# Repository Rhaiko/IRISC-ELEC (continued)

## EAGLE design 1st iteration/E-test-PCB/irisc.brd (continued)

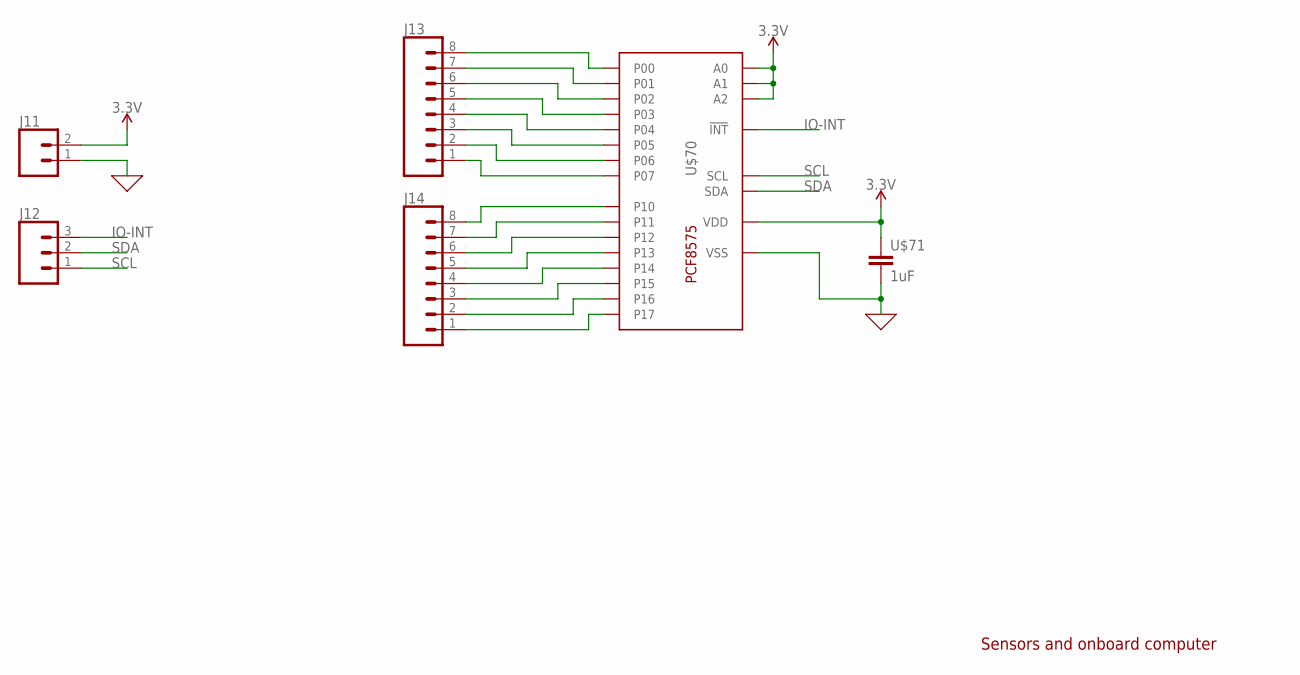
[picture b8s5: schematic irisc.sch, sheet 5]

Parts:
J11: CONN_02; 1X02
J12: CONN_03; 1X03
J13, J14: CONN_08"; 1X08
U$70: PCF8575CSSOP24N; SOP65P810X120-24
U$71: 1uF; RESC0603_N

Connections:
0: J11.1, U$70.12 (VSS), U$71.2; also elsewhere on the board
3.3V: J11.2, U$70.2 (A1), U$70.3 (A2), U$70.21 (A0), U$70.24 (VDD), U$71.1; also elsewhere on the board
IO-INT: J12.3, U$70.1 (!INT)
unnamed: J13.8, U$70.4 (P00)
unnamed: J13.7, U$70.5 (P01)
unnamed: J13.6, U$70.6 (P02)
unnamed: J13.5, U$70.7 (P03)
unnamed: J13.4, U$70.8 (P04)
unnamed: J13.3, U$70.9 (P05)
unnamed: J13.2, U$70.10 (P06)
unnamed: J13.1, U$70.11 (P07)
unnamed: J14.8, U$70.13 (P10)
unnamed: J14.7, U$70.14 (P11)
unnamed: J14.6, U$70.15 (P12)
unnamed: J14.5, U$70.16 (P13)
unnamed: J14.4, U$70.17 (P14)
unnamed: J14.3, U$70.18 (P15)
unnamed: J14.2, U$70.19 (P16)
unnamed: J14.1, U$70.20 (P17)
SCL: J12.1, U$70.22 (SCL); also elsewhere on the board
SDA: J12.2, U$70.23 (SDA); also elsewhere on the board

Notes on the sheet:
Sensors and onboard computer

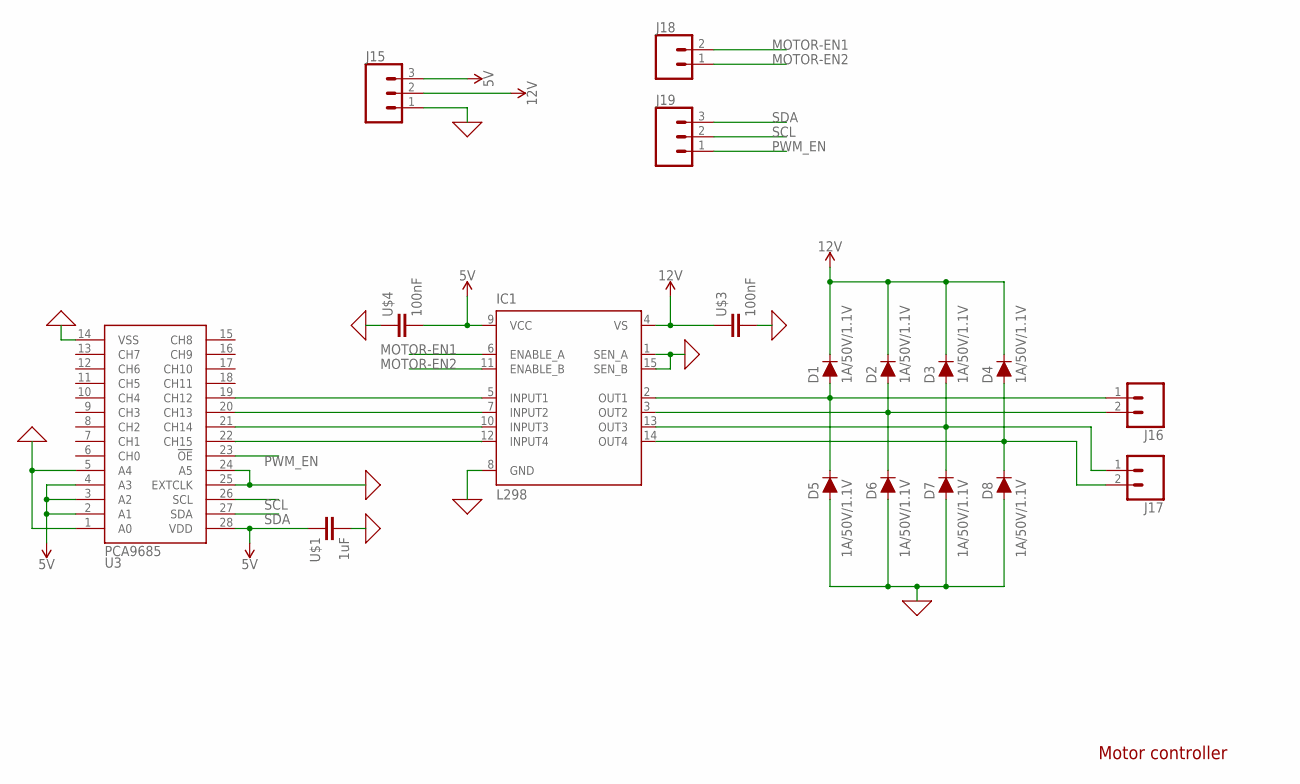
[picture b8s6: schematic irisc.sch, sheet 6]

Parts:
D1, D2, D3, D4, D5, D6, D7, D8: 1A/50V/1.1V; DIODE-1N4001
IC1: L298; MULTIWATT-15
J15, J19: CONN_03; 1X03
J16, J17: CONN_023.5MM; SCREWTERMINAL-3.5MM-2
J18: CONN_02; 1X02
U3: PCA9685; TSSOP-28_4MM
U$1: 1uF; RESC0805_L
U$3, U$4: 100nF; RESC0603_L

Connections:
0: D5.A, D6.A, D7.A, D8.A, IC1.1 (SEN_A), IC1.8 (GND), IC1.15 (SEN_B), J15.1, U3.1 (A0), U3.5 (A4), U3.14 (VSS), U3.24 (A5), U3.25 (EXTCLK), U$1.2, U$3.2, U$4.1; also elsewhere on the board
5V: IC1.9 (VCC), J15.3, U3.2 (A1), U3.3 (A2), U3.4 (A3), U3.28 (VDD), U$1.1, U$4.2; also elsewhere on the board
12V: D1.C, D2.C, D3.C, D4.C, IC1.4 (VS), J15.2, U$3.1
MOTOR-EN1: IC1.6 (ENABLE_A), J18.2
MOTOR-EN2: IC1.11 (ENABLE_B), J18.1
unnamed: IC1.5 (INPUT1), U3.19 (CH12)
unnamed: IC1.7 (INPUT2), U3.20 (CH13)
unnamed: IC1.10 (INPUT3), U3.21 (CH14)
unnamed: IC1.12 (INPUT4), U3.22 (CH15)
unnamed: D1.A, D5.C, IC1.2 (OUT1), J16.1
unnamed: D2.A, D6.C, IC1.3 (OUT2), J16.2
unnamed: D3.A, D7.C, IC1.13 (OUT3), J17.1
unnamed: D4.A, D8.C, IC1.14 (OUT4), J17.2
PWM_EN: J19.1, U3.23 (!OE)
SCL: J19.2, U3.26 (SCL); also elsewhere on the board
SDA: J19.3, U3.27 (SDA); also elsewhere on the board

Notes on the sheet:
Motor controller

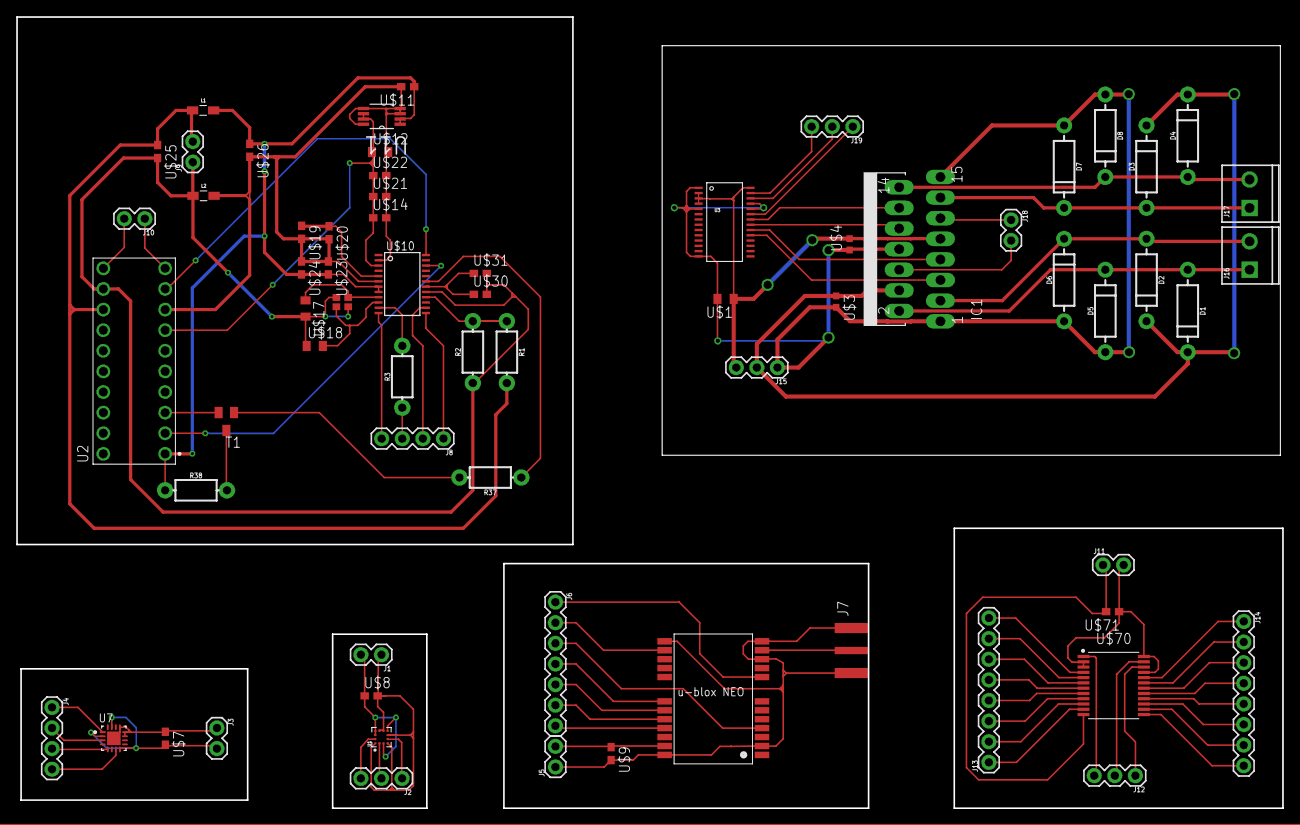
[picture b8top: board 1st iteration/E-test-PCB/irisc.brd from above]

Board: 2 copper layers, 156.0 x 97.5 mm, 67 parts (0 on the bottom side), 63 nets.

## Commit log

2019-01-07 first schematic
2019-01-13 Update motorcontroller, added sensors
2019-01-13 cleanup schematic
2019-01-21 Auto stash before merge of "master" and "origin/master"
2019-01-21 Revert "Merge branch 'master' into test"
    This reverts commit dfcaf70d8e9cfdf546262c8a169c9a7cbb3319ac.
2019-01-21 update embedded
2019-02-19 added schematics for 1st iteration PCB
2019-02-19 Removed unnecessary stuff in Elrick's 1st iteration PCB's
2019-04-02 1st iteration update, beginning of the PCB's
2019-04-02 E's systems almost done (only PCB gyro missing)
2019-04-02 Final E systems: schematics & PCB's
2019-04-11 Gerber files + total PCB
2019-08-20 Sabina Changes
